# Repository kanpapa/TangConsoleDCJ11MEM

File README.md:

# TangConsoleDCJ11MEM
DEC DCJ11 processor test board using memory systems and peripherals implemented  on Tang Console 138K.

This document is written mostly in Japanese. If necessary, please use a translation service such as DeepL or Google.

# 概要
- PDP-11の命令セットを持つCPU「DEC DCJ11」のメモリシステムと周辺装置をFPGAボード(Tang Console 138K)上に実装する試みです．
- TangNano20Kを用いた同様のプロジェクト[TangNanoDCJ11MEM](https://github.com/ryomuk/TangNanoDCJ11MEM)の続編です．

各種説明は[doc/](./doc/)にあるファイルに記載しています．

## 最近の話題
- 以前の話題は[更新ログ](doc/01_updatelog.md)参照
- 2025/10/17
  - 磁気テープリーダ(TM11)等を実装してunix v7や2.9BSDをインストール可能なバージョン(20251017)を公開しました．わりと大幅なアップデートです．
  - ブートローダーのアドレスを実物のROM(BM873-YA)に準拠させるように変更しました．主なアドレスは下記のようになっています．詳細は[doc/06-1-bootloader.md](doc/06-1-bootloader.md)を参照して下さい．
    - RK(unix v1): 773700
    - RP(unix v6, RT-11等): 773010
  - 説明文書を[doc/](./doc/)にまとめました．まだログファイルそのままだったりソースのコメントのコピペばかりですが，動かすのに必要な情報は揃っていると思います．気が向いたらもう少し書き直します．

## 主要なファイル一覧
```
.
├── diskimage : SDメモリ用データ
│   ├── Caldera-license.pdf : UNIXのライセンス条項
│   ├── sd-unix-v1.dsk      : unix v1用disk image
│   └── sd-unix-v6.dsk      : unix v6用disk image
├── doc                      : 説明用文書
│   ├── 01_updatelog.md
│   ├── 02_PCB.md
│   ├── 03_FPGA.md
│   ├── 04_Interface.md
│   ├── 05_SDmemory.md
│   ├── 06-0_applications.md
│   ├── 06-1_bootloader.md
│   ├── 06-2_papertapebasic.md
│   ├── 06-3_unix-v1.md
│   ├── 06-4_unix-v6.md
│   ├── 06-5_unix-v7.md
│   ├── 06_6_unix-2.9BSD.md
│   ├── 06_7_RT-11v4.md
│   ├── 07_debugtool
│   └── 08_references.md
├── hdl                      : Gowin EDA用プロジェクト
│   ├── old                 : 旧版のバックアップ(あれば)
│   └── TangConsoleDCJ11MEM_project.xxxxxxxx
│       └── src
│             ├── rom.v      : ブートローダー
│             ├── sdhd.v     : HDエミュレータモジュール
│             ├── sdtape.v   : 紙テープエミュレータモジュール
│             ├── tc138k.cst : 物理制約(ピンアサイン)
│             ├── top.v      : メインプログラム
│             ├── uart.v     : uartモジュール
│             └── ws2812.v   : WS2812モジュール
├── images                    : 文書用画像ファイル
├── pcb
│   └── rev2.0 : 回路図，基板データ等(KiCAD 8用)
└── README.md
```
- diskimageフォルダ内にあるSDメモリ用のイメージファイルはUNIXのオリジナルソースからの派生物なので，ライセンス条件は Caldera-license.pdf (昔のBSD?)に従います．
- その他の部分についてはMITライセンスです．

## 動作状況
- unix v1
  - multi userで起動，rootでログインできました．
  - edでASCIIARTのプログラムを書いてccでセルフコンパイルして実行できました．
- unix v6
  - multi userで起動，rootでログインできました．
  - /usr/games/ にあるchessやbj, tttなどが動きました．
  - 実機でカーネルの再構築ができました．
- paper tape
  - paper tape BASICが起動して簡単なプログラムが動作しました．
  - unix v1, unix v6のデバイスとして読むことができました．
- rt-11 v4
  - 起動してHELP, DIRが動きました．(top.vのオプションを変更してビルドする必要あり)
- unix v7  
  - ディストリビューションテープからインストールとブートができました．
- 2.9BSD
  - ディストリビューションテープからインストールとブートができました．
  
## 既知の問題
- 電源投入直後はブートに失敗することが多い気がします．Tang Console のreconfigボタン(pmodコネクタのあたりにあるやつ)を押してリセットしてからリトライすると直ることが多いです．
- v6のファイルシステムは壊れやすいような気がします．電源断前にはsync3〜4回のおまじないが必要かも．
- v7でハードディスクにddしたbootloaderがちゃんと動かないような気がします．tapeのブートローダーでブートできます．

## 開発環境
- Windows 11
  - KiCAD 8.0.5
  - GOWIN FPGA Designer V1.9.11.02(64-bit)
  - VMware Workstation 17 Player
    - Ubuntu 22.04.4
      - dd
      - simh
  - TeraTerm
  - PDP11GUI

# 動画
- [UNIX V6 on DEC DCJ-11 (PDP-11) with Tang Console 138K](https://www.youtube.com/watch?v=6rK0t8tJp9Y)

# 更新履歴
- 2025/09/03: 初版(20250922)公開
- 2025/09/06: unix v6でもccが動いたのでREADME修正．
- 2025/09/08: READMEに軽微な情報追加．
- 2025/09/22: 20250922版(pmod paper tape実装)暫定公開．(説明は未)
- 2025/09/26: 20250926版公開．(RT-11 v4起動)
- 2025/10/19: 20251017版公開．(磁気テープ実装, unix v7, 2.9BSD起動)
- 2025/10/19: ドキュメント構成見直し

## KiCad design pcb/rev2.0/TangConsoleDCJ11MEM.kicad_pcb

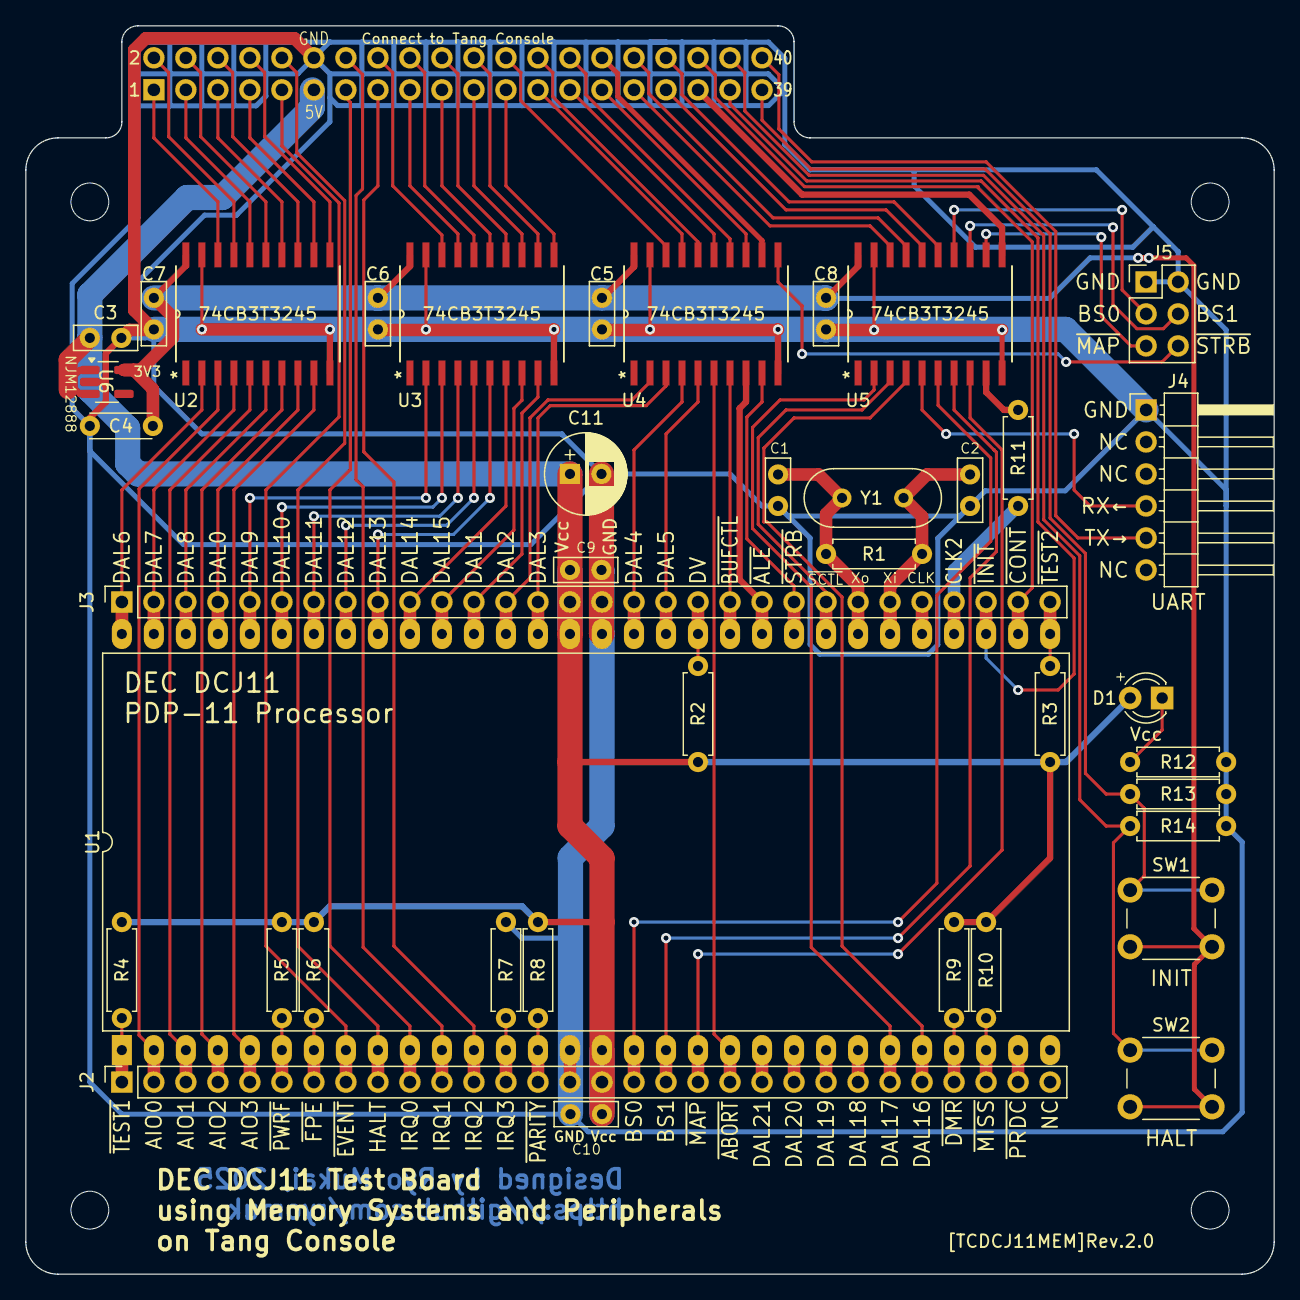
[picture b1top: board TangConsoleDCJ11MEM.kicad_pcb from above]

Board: 2 copper layers, 99.1 x 99.1 mm, 40 parts (1 on the bottom side), 96 nets.

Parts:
C1, C2: 68p; C_Disc_D5.0mm_W2.5mm_P2.50mm
C3, C5, C6, C7, C8: 0.1uF; C_Disc_D5.0mm_W2.5mm_P2.50mm
C4: 1uF; C_Disc_D4.7mm_W2.5mm_P5.00mm
C9, C10: 0.33uF; C_Disc_D5.0mm_W2.5mm_P2.50mm
C11: 47uF; CP_Radial_D6.3mm_P2.50mm
D1: LED; LED_D3.0mm
J1: Conn_02x20_Odd_Even; PinSocket_2x20_P2.54mm_Vertical
J2, J3: Conn_01x30; PinSocket_1x30_P2.54mm_Vertical
J4: UART; PinHeader_1x06_P2.54mm_Horizontal
J5: EXT; PinHeader_2x03_P2.54mm_Vertical
R1: 1M; R_Axial_DIN0207_L6.3mm_D2.5mm_P7.62mm_Horizontal
R2, R3, R4, R5, R6, R7, R8, R9, R10: 10k; R_Axial_DIN0207_L6.3mm_D2.5mm_P7.62mm_Horizontal
R11: 51; R_Axial_DIN0207_L6.3mm_D2.5mm_P7.62mm_Horizontal
R12: 100k; R_Axial_DIN0207_L6.3mm_D2.5mm_P7.62mm_Horizontal
R13, R14: 1k; R_Axial_DIN0207_L6.3mm_D2.5mm_P7.62mm_Horizontal
SW1: INIT; SW_PUSH_6mm_H4.3mm
SW2: HALT; SW_PUSH_6mm_H4.3mm
U1: DCJ11; DIP-60_W33.02mm_LongPads
U2, U3, U4, U5: SN74CB3T3245DW; DW20
U6: NJM12888F33-TE1; SOT-23-5_HandSoldering
Y1: 18MHz; Crystal_HC49-U_Vertical

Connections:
+3.3V: C4.1, C5.1, C6.1, C7.1, C8.1, SW1.2, SW2.2, U2.20 (VCC), U3.20 (VCC), U4.20 (VCC), U5.20 (VCC), U6.5 (VOUT)
+5V: C3.1, C9.1, C10.1, C11.1, D1.2 (A), J1.11, J2.16, J3.15, R2.2, R3.2, R4.2, R5.2, R6.2, R8.2, R9.2, R10.2, U1.16 (VCC), U1.46 (VCC), U6.1 (VIN), U6.3 (CONTROL)
ABORT_n: J2.20, U1.20 (~ABORT), U4.6 (A5)
ABORT_n_L: J1.28, U4.14 (B5)
AIO0: J2.2, U1.2 (AIO0), U2.3 (A2)
AIO0_L: J1.2, U2.17 (B2)
AIO1: J2.3, U1.3 (AIO1), U2.5 (A4)
AIO1_L: J1.4, U2.15 (B4)
AIO2: J2.4, U1.4 (AIO2), U2.7 (A6)
AIO2_L: J1.6, U2.13 (B6)
AIO3: J2.5, U1.5 (AIO3), U2.9 (A8)
AIO3_L: J1.8, U2.11 (B8)
ALE_n: J3.21, U1.40 (~ALE), U4.8 (A7)
ALE_n_L: J1.30, U4.12 (B7)
BS0: J2.17, U1.17 (BS0), U5.6 (A5)
BS0_L: J5.3, U5.14 (B5)
BS1: J2.18, U1.18 (BS1), U5.7 (A6)
BS1_L: J5.4, U5.13 (B6)
BUFCTL_n: J3.20, U1.41 (~BUFCTL), U4.7 (A6)
BUFCTL_n_L: J1.29, U4.13 (B6)
CLK: J3.26, U1.35 (CLK)
CLK2: J3.27, R11.1, U1.34 (CLK2)
CLK2_L: J1.35, U5.11 (B8)
CONT_n: J1.36, J3.29, U1.32 (CONT)
DAL0: J3.4, U1.57 (DAL0), U2.8 (A7)
DAL0_L: J1.7, U2.12 (B7)
DAL1: J3.12, U1.49 (DAL1), U3.9 (A8)
DAL1_L: J1.23, U3.11 (B8)
DAL2: J3.13, U1.48 (DAL2), U4.2 (A1)
DAL2_L: J1.24, U4.18 (B1)
DAL3: J3.14, U1.47 (DAL3), U4.3 (A2)
DAL3_L: J1.25, U4.17 (B2)
DAL4: J3.17, U1.44 (DAL4), U4.4 (A3)
DAL4_L: J1.26, U4.16 (B3)
DAL5: J3.18, U1.43 (DAL5), U4.5 (A4)
DAL5_L: J1.27, U4.15 (B4)
DAL6: J3.1, U1.60 (DAL6), U2.2 (A1)
DAL6_L: J1.1, U2.18 (B1)
DAL7: J3.2, U1.59 (DAL7), U2.4 (A3)
DAL7_L: J1.3, U2.16 (B3)
DAL8: J3.3, U1.58 (DAL8), U2.6 (A5)
DAL8_L: J1.5, U2.14 (B5)
DAL9: J3.5, U1.56 (DAL9), U3.2 (A1)
DAL9_L: J1.16, U3.18 (B1)
DAL10: J3.6, U1.55 (DAL10), U3.3 (A2)
DAL10_L: J1.17, U3.17 (B2)
DAL11: J3.7, U1.54 (DAL11), U3.4 (A3)
DAL11_L: J1.18, U3.16 (B3)
DAL12: J3.8, U1.53 (DAL12), U3.5 (A4)
DAL12_L: J1.19, U3.15 (B4)
DAL13: J3.9, U1.52 (DAL13), U3.6 (A5)
DAL13_L: J1.20, U3.14 (B5)
DAL14: J3.10, U1.51 (DAL14), U3.7 (A6)
DAL14_L: J1.21, U3.13 (B6)
DAL15: J3.11, U1.50 (DAL15), U3.8 (A7)
DAL15_L: J1.22, U3.12 (B7)
DAL16: J2.26, U1.26 (DAL16), U5.4 (A3)
DAL16_L: J1.33, U5.16 (B3)
DAL17: J2.25, U1.25 (DAL17), U5.2 (A1)
DAL17_L: J1.31, U5.18 (B1)
DAL18: J2.24, U1.24 (DAL18)
DAL19: J2.23, U1.23 (DAL19)
DAL20: J2.22, U1.22 (DAL20)
DAL21: J2.21, U1.21 (DAL21)
DMR_n: J2.27, R9.1, U1.27 (~DMR)
DV: J3.19, R2.1, U1.42 (DV)
EVENT_n: J1.9, J2.8, U1.8 (~EVENT)
FPE_n: J2.7, R6.1, U1.7 (~FPE)
GND: C1.1, C2.1, C3.2, C4.2, C5.2, C6.2, C7.2, C8.2, C9.2, C10.2, C11.2, J1.12, J2.15, J3.16, J4.1, J5.1, J5.2, R7.2, R12.1, R13.1, R14.1, U1.15 (GND), U1.45 (GND), U2.10 (GND), U2.19 (*OE), U3.10 (GND), U3.19 (*OE), U4.10 (GND), U4.19 (*OE), U5.10 (GND), U5.19 (*OE), U6.2 (GND)
GPIO_RX: J4.4, U5.5 (A4)
GPIO_RX_L: J1.34, U5.15 (B4)
GPIO_TX: J1.40, J4.5
HALT: J1.10, J2.9, U1.9 (HALT)
HALT_SW: J1.38, R14.2, SW2.1
INIT_SW: J1.39, R13.2, SW1.1
INIT_n: J1.37, J3.28, U1.33 (~INIT)
IRQ0: J1.13, J2.10, U1.10 (IRQ0)
IRQ1: J1.14, J2.11, U1.11 (IRQ1)
IRQ2: J1.15, J2.12, U1.12 (IRQ2)
IRQ3: J2.13, R7.1, U1.13 (IRQ3)
MAP_n: J2.19, U1.19 (~MAP), U5.8 (A7)
MAP_n_L: J5.5, U5.12 (B7)
MISS_n: J2.28, R10.1, U1.28 (~MISS)
unnamed: D1.1 (K), R12.2
unnamed: R11.2, U5.9 (A8)
PARITY_n: J2.14, R8.1, U1.14 (~PARITY)
PRDC_n: J2.29, U1.29 (~PRDC)
PWRF_n: J2.6, R5.1, U1.6 (~PWRF)
SCTL_n: J3.23, U1.38 (~SCTL), U5.3 (A2)
SCTL_n_L: J1.32, U5.17 (B2)
STRB_n: J3.22, U1.39 (~STRB), U4.9 (A8)
STRB_n_L: J5.6, U4.11 (B8)
TEST1_n: J2.1, R4.1, U1.1 (~TEST1)
TEST2_n: J3.30, R3.1, U1.31 (~TEST2)
XTALI: C2.2, J3.25, R1.2, U1.36 (XTALI), Y1.1
XTALO: C1.2, J3.24, R1.1, U1.37 (XTALO), Y1.2

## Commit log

2025-09-02 Update LICENSE
2025-09-02 Create LICENSE-UNIX
    added LICENSE-UNIX
2025-09-04 README updated
2025-09-22 folder name changed
2025-09-22 20250922 pre-released
2025-09-26 gitignore updated
2025-09-26 20250926 released
2025-09-29 config file added
2025-10-18 20251017 released
2025-10-18 old file removed
2025-10-18 document updated
2025-10-19 Fixed the broken link
2025-10-23 J4 was not displayed in the BOM, so I fixed it.
